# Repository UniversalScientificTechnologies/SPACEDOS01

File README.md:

# SPACEDOS01B - Cosmic-ray spectrometer and dosimeter for unmanned spacecraft missions

SPACEDOS01B is a semiconductor-based dosimeter launched at Sokrat-R (NORAD ID 44404) satellite, currently orbiting the Earth about 500km above the surface.
The device is intended for the measurement of cosmic radiation in mixed ionization fields on board satellites. In the case of manned missions look to [SPACEDOS02](https://github.com/UniversalScientificTechnologies/SPACEDOS02) or [SPACEDOS03](https://github.com/UniversalScientificTechnologies/SPACEDOS03).

The device can be purchased from Universal Scientific Technologies s.r.o. Contact us by email at sale@ust.cz for a commercial quotation.

### The main technical parameters are the following

* Silicon PIN diode detector with ~12.5 mm³ detection volume
* Measurement environment: vacuum < 3.2×10e−2 Pa
* Number of energy channels: 250
* Deposited energy range: from 200 keV to 12 MeV
* Energy measurement resolution: < 50 keV/channel
* Power supply: 3.3 V / 3 mA
* Integration time: 15 s
* Interface: RS232 TTL
* Dimensions(HxWxL): 15mm x 41mm x 94 mm
* Weight 33 g

[Technical documentation](https://docs.dos.ust.cz/spacedos/SPACEDOS01)

## References

  * [SPACEDOS dosimeter from the NPI became a part of the Cosmos Discovery exhibition](http://www.ujf.cas.cz/en/news/SPACEDOS-dosimeter-from-the-NPI-became-a-part-of-the-Cosmos-Discovery-exhibition/)
  * [SPACEDOS an open-source PIN diode dosimeter for applications in Space](https://indico.ujf.cas.cz/event/2/contributions/27/attachments/25/46/Po-1315-Kakona-774711333.pdf)

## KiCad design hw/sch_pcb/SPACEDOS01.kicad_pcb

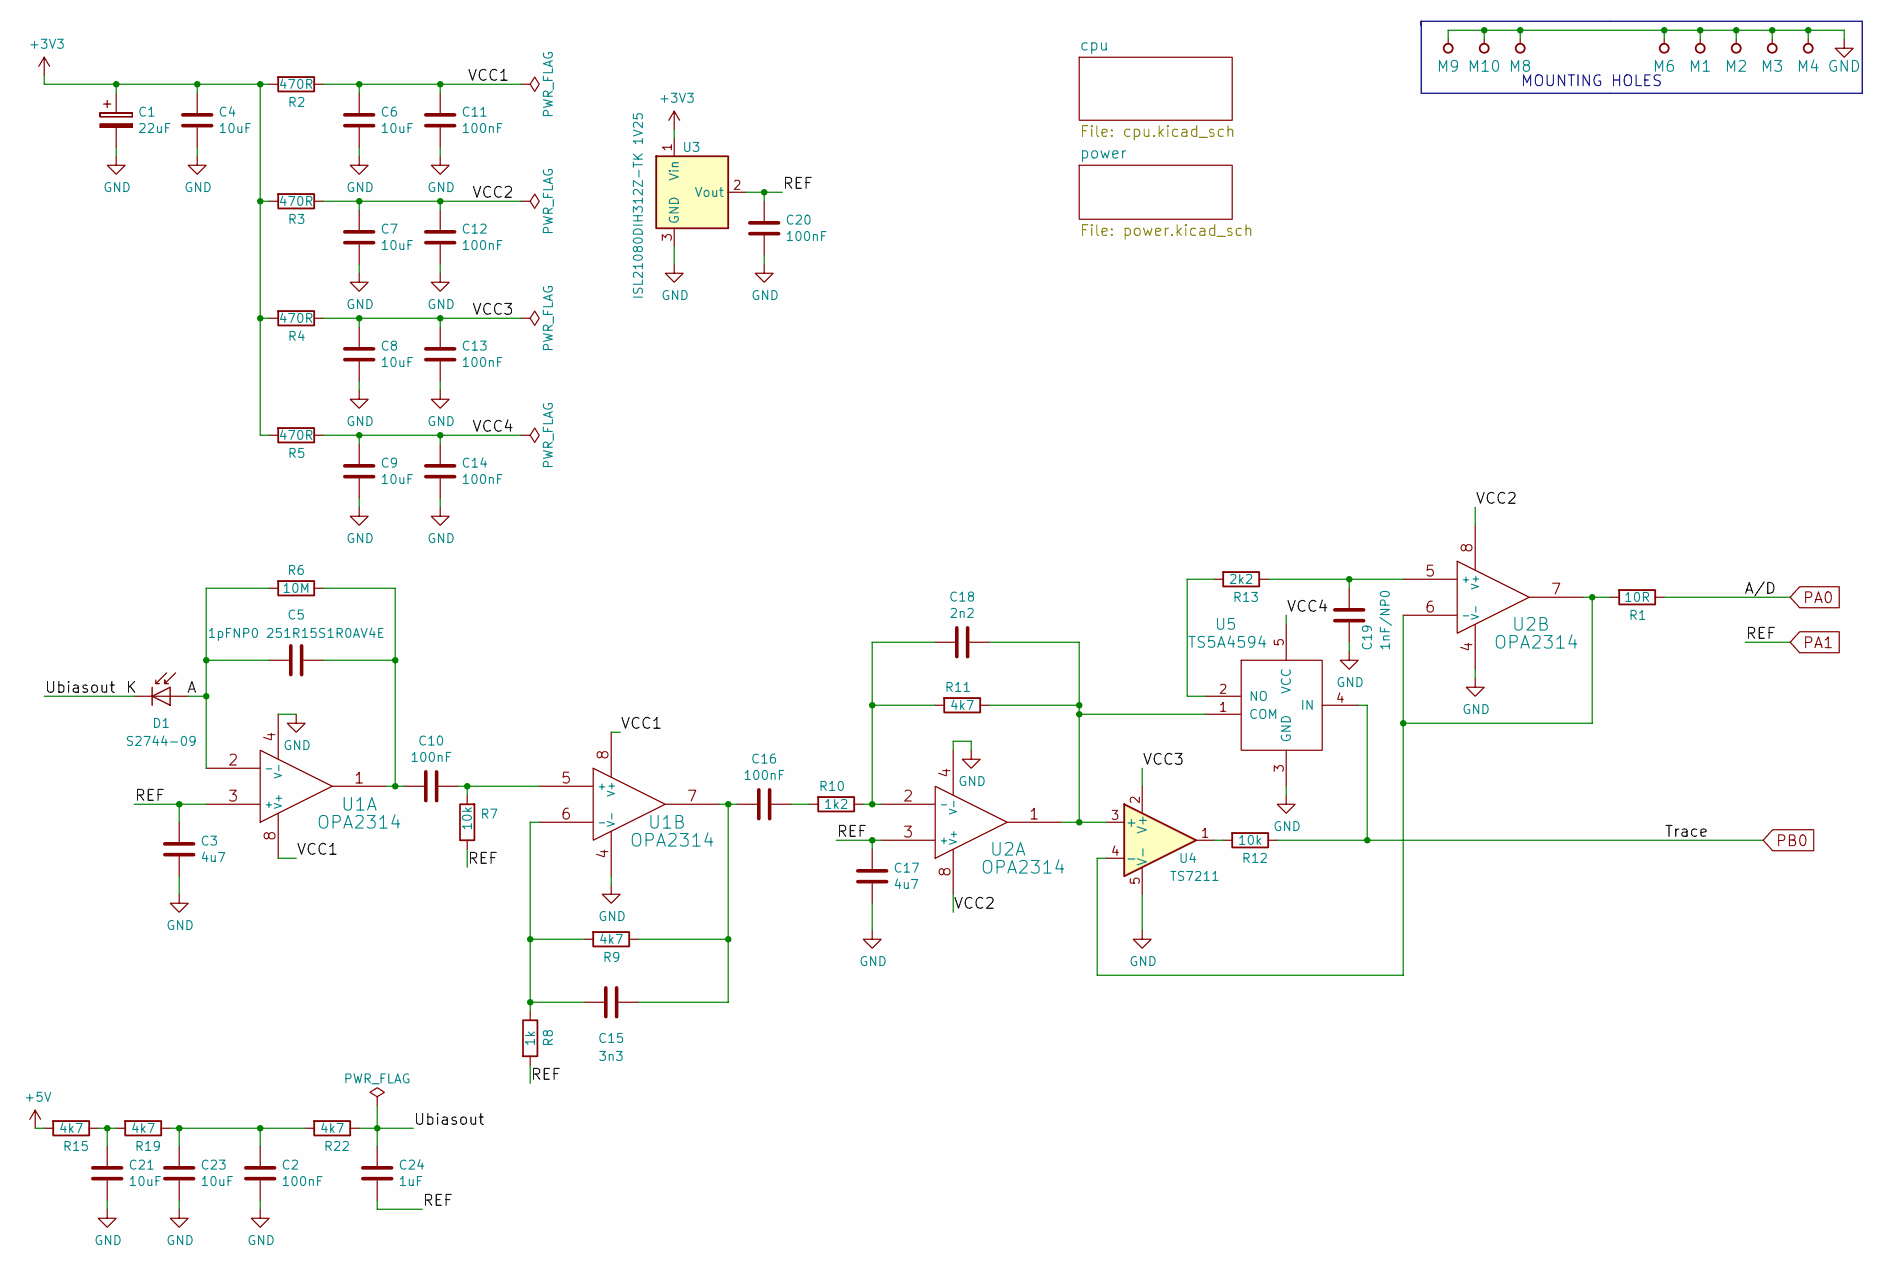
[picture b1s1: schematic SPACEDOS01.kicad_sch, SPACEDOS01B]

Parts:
C1: 22uF; TantalC_SizeC_Reflow
C2, C10, C11, C12, C13, C14, C16, C20: 100nF; SMD-0805
C3, C17: 4u7; SMD-0805
C4, C6, C7, C8, C9, C21, C23: 10uF; SMD-0805
C5: 1pFNP0 251R15S1R0AV4E; SMD-0805
C15: 3n3; SMD-0805
C18: 2n2; SMD-0805
C19: 1nF/NP0; SMD-0805
C24: 1uF; SMD-0805
D1: S2744-09; HAMAMATSU_S11773-02
M1, M2, M3, M4: HOLE; MountingHole_3mm
M6: BMI-S-210-F
M8, M9, M10: BMI-S-204-F; Laird_Technologies_BMI-S-204-F_32.00x32.00mm
R1: 10R; SMD-0805
R2, R3, R4, R5: 470R; SMD-0805
R6: 10M; SMD-0805
R7, R12: 10k; SMD-0805
R8: 1k; SMD-0805
R9, R11, R15, R19, R22: 4k7; SMD-0805
R10: 1k2; SMD-0805
R13: 2k2; SMD-0805
U1, U2: OPA2314; SOIC-8_3.9x4.9mm_Pitch1.27mm
U3: ISL21080DIH312Z-TK 1V25; SOT-23
U4: TS7211; SOT-23-5_HandSoldering
U5: TS5A4594; SOT-23-5_HandSoldering

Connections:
+3V3: C1.1, C4.1, R2.2, R3.2, R4.2, R5.2, U3.1 (Vin); also elsewhere on the board
+5V: R15.2; also elsewhere on the board
/A: C5.2, D1.2 (A), R6.2, U1.2 (-)
/K: C24.1, D1.1 (K), R22.1
/VCC1: C6.1, C11.1, R2.1, U1.8 (V+)
/VCC2: C7.1, C12.1, R3.1, U2.8 (V+)
/VCC3: C8.1, C13.1, R4.1, U4.2 (V+)
/VCC4: C9.1, C14.1, R5.1, U5.5 (VCC)
GND: C1.2, C2.2, C3.2, C4.2, C6.2, C7.2, C8.2, C9.2, C11.2, C12.2, C13.2, C14.2, C17.2, C19.2, C20.2, C21.2, C23.2, M1.1, M2.1, M3.1, M4.1, M6.1, M8.1, M9.1, M10.1, U1.4 (V-), U2.4 (V-), U3.3 (GND), U4.5 (V-), U5.3 (GND); also elsewhere on the board
unnamed: C2.1, C23.1, R19.1, R22.2
unnamed: C5.1, C10.2, R6.1, U1.1
unnamed: C15.1, C16.2, R9.1, U1.7
unnamed: C16.1, R10.2
unnamed: C21.1, R15.1, R19.2
unnamed: R12.2, U4.1
unnamed: C10.1, R7.2, U1.5 (+)
unnamed: C15.2, R8.1, R9.2, U1.6 (-)
unnamed: C18.2, R10.1, R11.2, U2.2 (-)
unnamed: C19.1, R13.1, U2.5 (+)
unnamed: R1.2, U2.6 (-), U2.7, U4.4 (-)
unnamed: C18.1, R11.1, U2.1, U4.3 (+), U5.1 (COM)
unnamed: R13.2, U5.2 (NO)
PA0: R1.1; also elsewhere on the board
PA1: C3.1, C17.1, C20.1, C24.2, R7.1, R8.2, U1.3 (+), U2.3 (+), U3.2 (Vout); also elsewhere on the board
PB0: R12.1, U5.4 (IN); also elsewhere on the board

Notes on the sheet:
MOUNTING HOLES

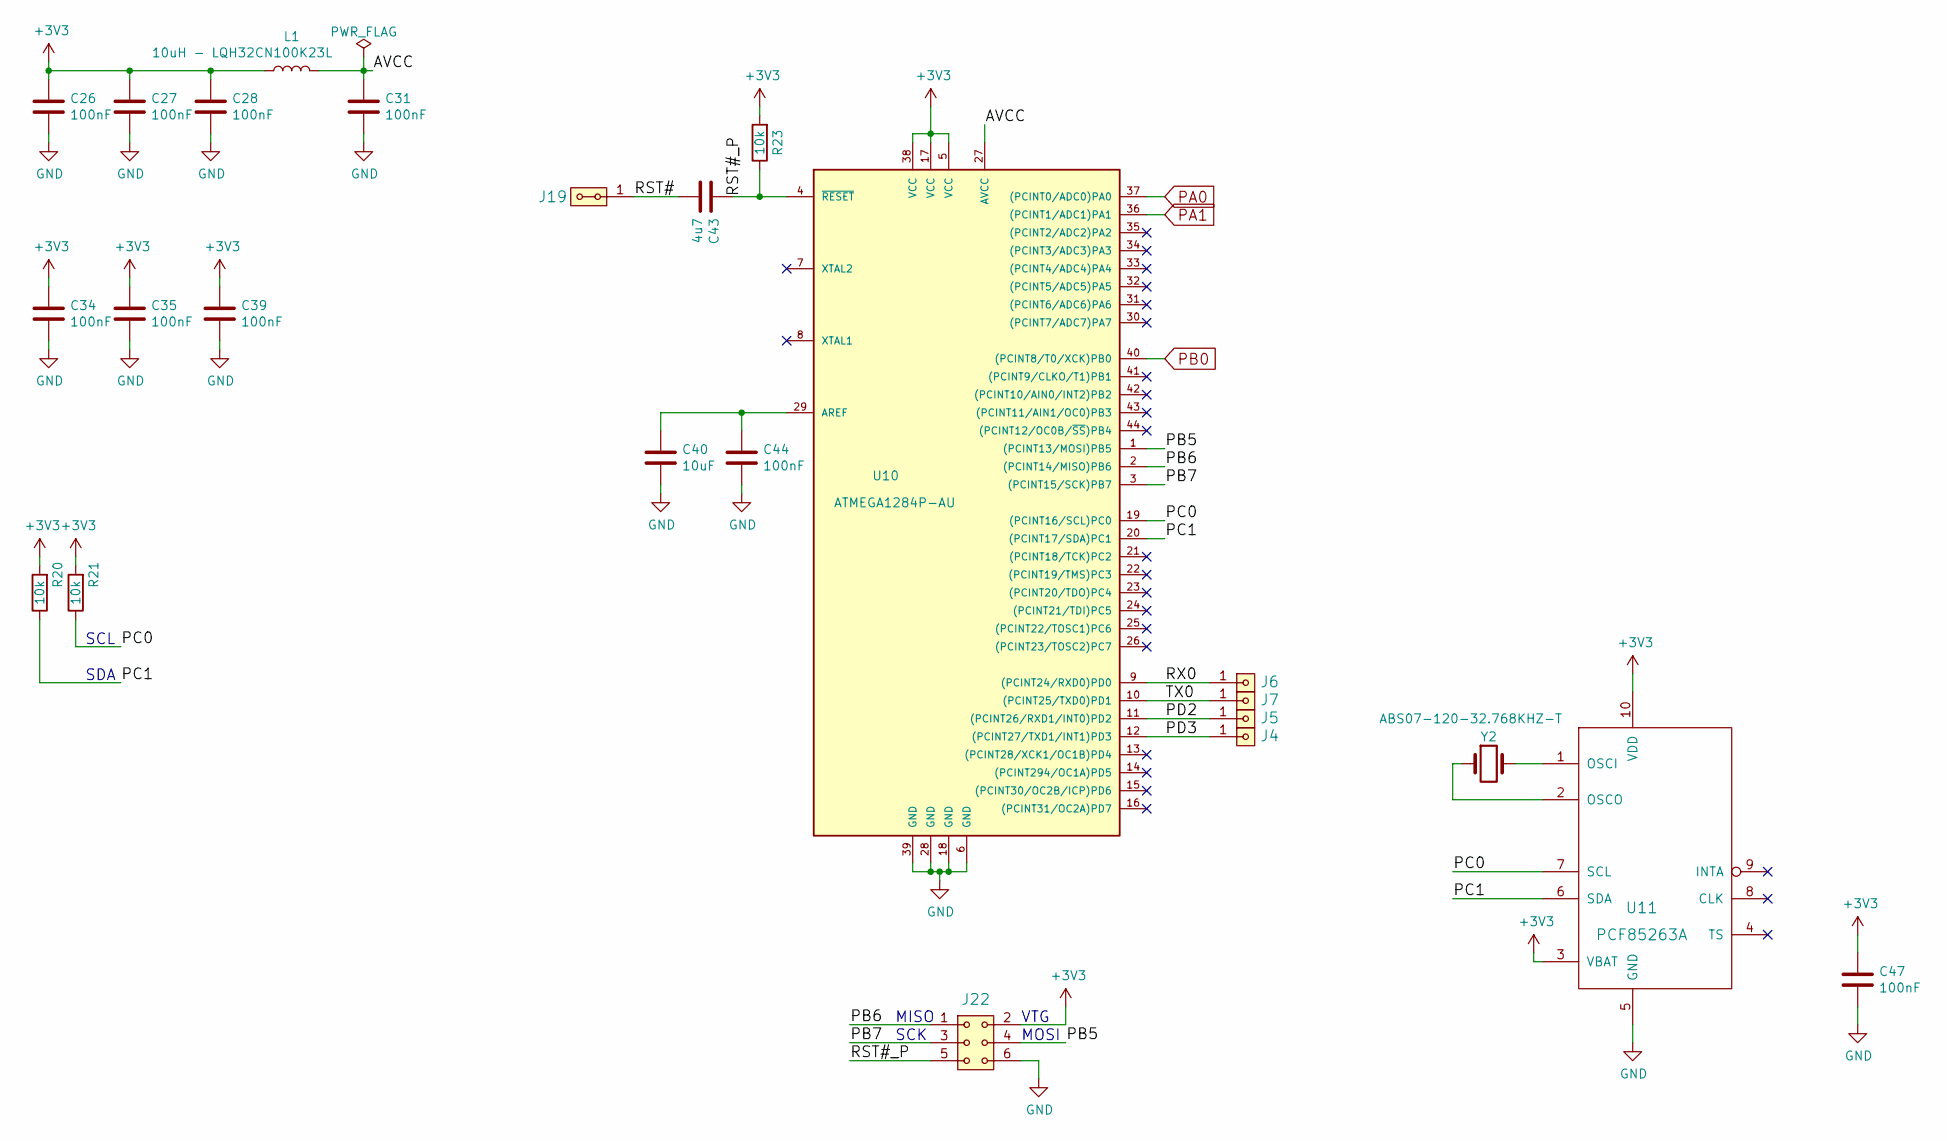
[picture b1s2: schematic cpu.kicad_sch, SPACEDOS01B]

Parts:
C26, C27, C28, C31, C34, C35, C39, C44, C47: 100nF; SMD-0805
C40: 10uF; SMD-0805
C43: 4u7; SMD-0805
J4, J5, J6, J7: HEADER_1x01; Straight_1x01
J19: HEADER_2x01_PARALLEL; Straight_2x01
J22: HEADER_2x03; SMD_2x03
L1: 10uH - LQH32CN100K23L; SMD-1210
R20, R21, R23: 10k; SMD-0805
U10: ATMEGA1284P-AU; TQFP-44_10x10mm_P0.8mm
U11: PCF85263A; TSSOP-10_3x3mm_Pitch0.5mm
Y2: ABS07-120-32.768KHZ-T; ABS07

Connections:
+3V3: C26.1, C27.1, C28.1, C34.1, C35.1, C39.1, C47.1, J22.2, L1.1, R20.2, R21.2, R23.2, U10.5 (VCC), U10.17 (VCC), U10.38 (VCC), U11.3 (VBAT), U11.10 (VDD); also elsewhere on the board
/cpu/AVCC: C31.1, L1.2, U10.27 (AVCC)
/cpu/PB5: J22.4, U10.1 ((PCINT13/MOSI)PB5)
/cpu/PB6: J22.1, U10.2 ((PCINT14/MISO)PB6)
/cpu/PB7: J22.3, U10.3 ((PCINT15/SCK)PB7)
/cpu/PC0: R21.1, U10.19 ((PCINT16/SCL)PC0), U11.7 (SCL)
/cpu/PC1: R20.1, U10.20 ((PCINT17/SDA)PC1), U11.6 (SDA)
/cpu/PD2: J5.1, U10.11 ((PCINT26/RXD1/INT0)PD2)
/cpu/PD3: J4.1, U10.12 ((PCINT27/TXD1/INT1)PD3)
/cpu/RST#: C43.2, J19.1, J19.2
/cpu/RST#_P: C43.1, J22.5, R23.1, U10.4 (~RESET)
/cpu/RX0: J6.1, U10.9 ((PCINT24/RXD0)PD0)
/cpu/TX0: J7.1, U10.10 ((PCINT25/TXD0)PD1)
GND: C26.2, C27.2, C28.2, C31.2, C34.2, C35.2, C39.2, C40.2, C44.2, C47.2, J22.6, U10.6 (GND), U10.18 (GND), U10.28 (GND), U10.39 (GND), U11.5 (GND); also elsewhere on the board
unnamed: C40.1, C44.1, U10.29 (AREF)
unnamed: U11.1 (OSCI), Y2.2
unnamed: U11.2 (OSCO), Y2.1
PA0: U10.37 ((PCINT0/ADC0)PA0); also elsewhere on the board
PA1: U10.36 ((PCINT1/ADC1)PA1); also elsewhere on the board
PB0: U10.40 ((PCINT8/T0/XCK)PB0); also elsewhere on the board

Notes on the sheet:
SCL
MISO
MOSI
SCK
SDA
VTG

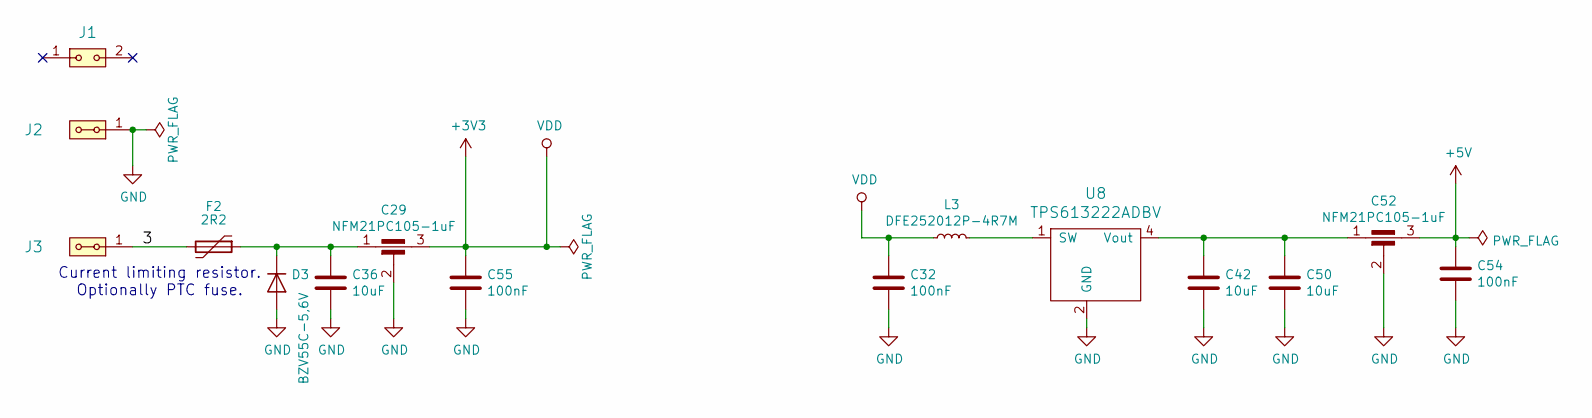
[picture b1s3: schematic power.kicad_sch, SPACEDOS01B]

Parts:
C29, C52: NFM21PC105-1uF; FIR_0805
C32, C54, C55: 100nF; SMD-0805
C36, C42, C50: 10uF; SMD-0805
D3: BZV55C-5,6V; D_MiniMELF
F2: 2R2; SMD-0805
J1: HEADER_2x01; Straight_1x02
J2, J3: HEADER_2x01_PARALLEL; Straight_1x02
L3: DFE252012P-4R7M; R_0805_2012Metric_Pad1.15x1.40mm_HandSolder
U8: TPS613222ADBV; SOT-23-5

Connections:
+3V3: C29.3, C32.1, C55.1, L3.1; also elsewhere on the board
+5V: C52.3, C54.1; also elsewhere on the board
/power/3: F2.2, J3.1, J3.2
GND: C29.2, C32.2, C36.2, C42.2, C50.2, C52.2, C54.2, C55.2, D3.2 (A), J2.1, J2.2, U8.2 (GND); also elsewhere on the board
unnamed: C29.1, C36.1, D3.1 (K), F2.1
unnamed: L3.2, U8.1 (SW)
unnamed: C42.1, C50.1, C52.1, U8.4 (Vout)

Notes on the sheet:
Current limiting resistor. Optionally PTC fuse.

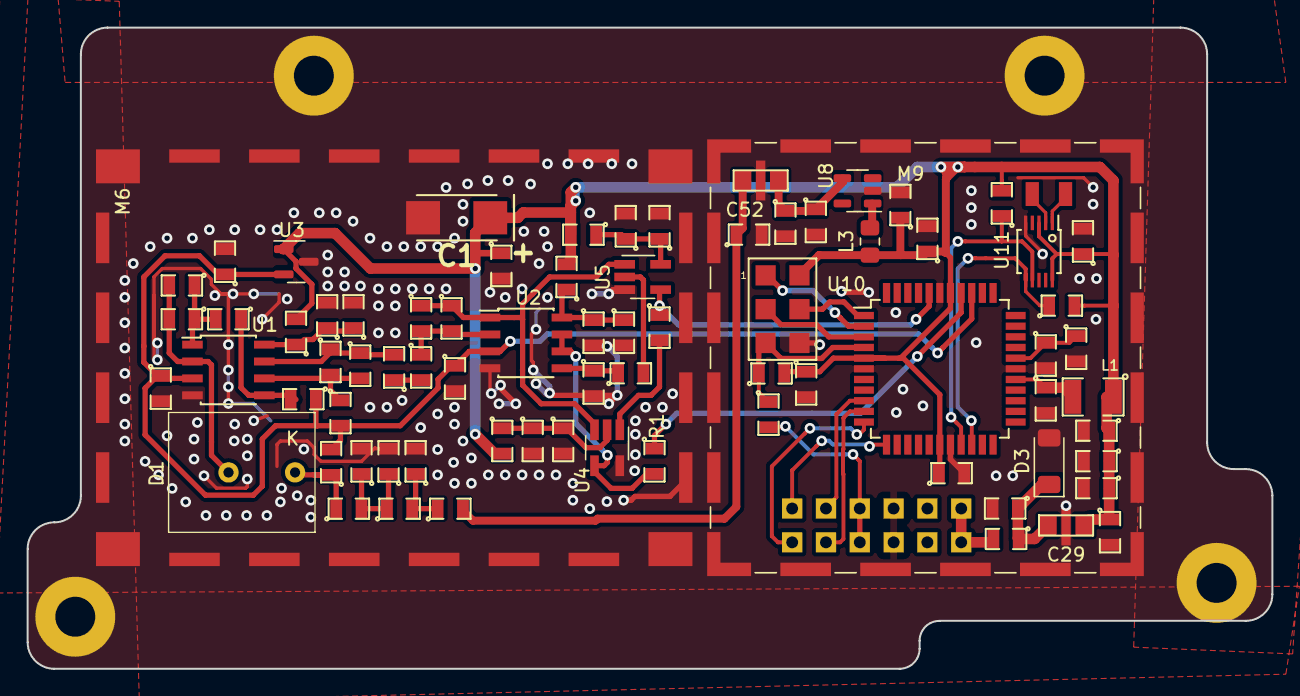
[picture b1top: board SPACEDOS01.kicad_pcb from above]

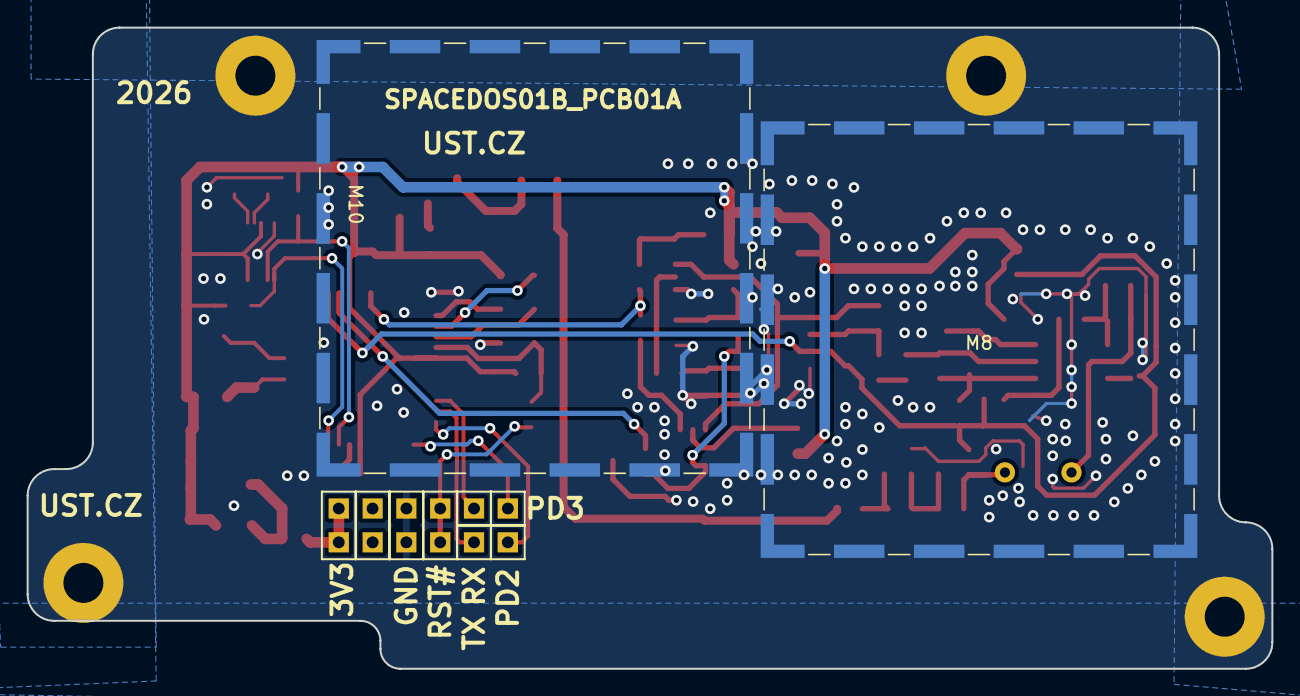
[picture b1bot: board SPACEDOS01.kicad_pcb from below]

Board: 2 copper layers, 93.5 x 48.2 mm, 92 parts (10 on the bottom side), 44 nets.

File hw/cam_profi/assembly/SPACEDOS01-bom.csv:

Component,Description,Part,References,Value,Footprint,Quantity Per PCB,Datasheet,ust_id
1,,C,C18,2n2,SMD-0805,1,~,5c70984712875079b91f8b46
2,,C,C15,3n3,SMD-0805,1,~,5c70984712875079b91f8b47
3,,C,C2C10C11C12C13C14C16C20,100nF,SMD-0805,8,,5c70984712875079b91f8b4c
4,,C-device-DATALOGGER01A-rescue-CCP2019V01A-rescue-SPACEDOS01A_PCB01A-rescue,C26C27C28C31C32C34C35C39C44C47C54C55,100nF,SMD-0805,12,,5c70984712875079b91f8b4c
5,,C,C24,1uF,SMD-0805,1,~,5c70984712875079b91f8b50
6,,C,C3C17,4u7,SMD-0805,2,~,5e3ff8fc1287502a33bad7a3
7,,C-device-DATALOGGER01A-rescue-CCP2019V01A-rescue-SPACEDOS01A_PCB01A-rescue,C43,4u7,SMD-0805,1,,5e3ff8fc1287502a33bad7a3
8,,C,C4C6C7C8C9C21C23,10uF,SMD-0805,7,~,5c70984712875079b91f8b53
9,,C-device-DATALOGGER01A-rescue-CCP2019V01A-rescue-SPACEDOS01A_PCB01A-rescue,C36C40C42C50,10uF,SMD-0805,4,,5c70984712875079b91f8b53
10,,CP,C1,22uF,TantalC_SizeC_Reflow,1,~,650b58f1462c6d9e7205463b
11,,C,C19,1nF/NP0,SMD-0805,1,~,5c70984812875079b91f8ba6
12,,C,C5,1pFNP0 251R15S1R0AV4E,SMD-0805,1,~,5c70984712875079b91f8b9f
13,,EMI_Filter_C-device-DATALOGGER01A-rescue-CCP2019V01A-rescue-SPACEDOS01A_PCB01A-rescue,C29C52,NFM21PC105-1uF,FIR_0805,2,http://www.murata.com/~/media/webrenewal/support/library/cat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,5c70984412875079b91f880f
14,,D-device-DATALOGGER01A-rescue-CCP2019V01A-rescue-SPACEDOS01A_PCB01A-rescue,D3,"BZV55C-5,6V",D_MiniMELF,1,,5c70984512875079b91f88b2
15,,D_Photo,D1,S2744-09,HAMAMATSU_S11773-02,1,~,628d118cdc56076e9a2235e4
16,,Polyfuse-device-DATALOGGER01A-rescue-CCP2019V01A-rescue-SPACEDOS01A_PCB01A-rescue-SPACEDOS01B_PCB01A-rescue,F2,2R2,SMD-0805,1,,5cac42d21287500e61c241e5
17,,L-device-DATALOGGER01A-rescue-CCP2019V01A-rescue-SPACEDOS01A_PCB01A-rescue,L1,10uH - LQH32CN100K23L,SMD-1210,1,,5c70984412875079b91f87ff
18,,L_Small,L3,DFE252012P-4R7M,R_0805_2012Metric_Pad1.15x1.40mm_HandSolder,1,~,5cc3309d128750448e54e8d8
19,,HOLE,M8M9M10,BMI-S-204-F,Laird_Technologies_BMI-S-204-F_32.00x32.00mm,3,,5c72751c1287500b4e11301a
20,,HOLE,M6,BMI-S-210-F,BMI-S-210-F,1,,5c70984312875079b91f873d
21,,R,R1,10R,SMD-0805,1,~,5c70984512875079b91f896d
22,,R,R2R3R4R5,470R,SMD-0805,4,~,5c70984512875079b91f8986
23,,R,R8,1k,SMD-0805,1,~,5c70984512875079b91f898c
24,,R,R10,1k2,SMD-0805,1,~,5c70984512875079b91f898d
25,,R,R13,2k2,SMD-0805,1,~,5c70984612875079b91f8990
26,,R,R9R11R15R19R22,4k7,SMD-0805,5,~,5c70984612875079b91f8995
27,,R,R7R12,10k,SMD-0805,2,~,5c70984612875079b91f899f
28,,R-device-DATALOGGER01A-rescue-CCP2019V01A-rescue-SPACEDOS01A_PCB01A-rescue,R20R21R23,10k,SMD-0805,3,,5c70984612875079b91f899f
29,,R,R6,10M,SMD-0805,1,~,5c70984712875079b91f8aae
30,,ATMEGA1284P-AU-atmel-DATALOGGER01A-rescue-CCP2019V01A-rescue-SPACEDOS01A_PCB01A-rescue,U10,ATMEGA1284P-AU,TQFP-44_10x10mm_P0.8mm,1,http://www.atmel.com/Images/Atmel-8272-8-bit-AVR-microcontro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,5c70984712875079b91f8b5b
31,,ISL21070CIH320Z-TK,U3,ISL21080DIH312Z-TK  1V25,SOT-23,1,https://eu.mouser.com/datasheet/2/698/REN_isl21080_DST_20040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,5c70984712875079b91f8b7a
32,,AD8692,U1U2,OPA2314,SOIC-8_3.9x4.9mm_Pitch1.27mm,2,,5c70984412875079b91f879b
33,,PCF85263A,U11,PCF85263A,TSSOP-10_3x3mm_Pitch0.5mm,1,,5c70984612875079b91f8a0c
34,,TPS61322xA,U8,TPS613222ADBV,SOT-23-5,1,https://www.ti.com/lit/ds/symlink/tps61322.pdf,5c7190ae1287500b4e112e04
35,,TS5A4594,U5,TS5A4594,SOT-23-5_HandSoldering,1,,5c70984612875079b91f8a0d
36,,OP179GRT,U4,TS7211,SOT-23-5_HandSoldering,1,http://www.analog.com/media/en/technical-documentation/data-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,5c70984712875079b91f8b5b
37,,Crystal-device-DATALOGGER01A-rescue-CCP2019V01A-rescue-SPACEDOS01A_PCB01A-rescue,Y2,ABS07-120-32.768KHZ-T,ABS07,1,,5c70984712875079b91f8b1b

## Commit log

2019-01-30 New PCB
2019-01-30 edit
2019-02-11 first version for integration by ESC
2019-02-11 picture
2019-02-11 physical dimensions
2019-02-11 new picture
2019-02-11 connector header
2019-02-13 STEP and WRML models ware added
2019-02-27 test version with beacon data and almanac data
2019-03-01 Cvak, Hmmm to
2019-03-01 all hexadecimal output
2019-03-01 bath for githas renewing
2019-03-01 githash test
2019-03-06 edit PCB
2019-03-07 version hash scripts
2019-03-07 STEP format was generated
2019-03-11 pictures of version 01B
2019-03-14 with one day periodicity
2019-03-14 FW for calibration and gitattributes for branch master
2019-03-14 new GPIO ports definition for SPACEDOS01B
2019-03-14 bat name of .gitattributes
2019-07-03 Update of device photos.
2019-07-03 Removing old photo.
2020-11-24 Edit PCB SPACEDOS01A_PCB01B
2020-11-25 Editace PCB a generování vyrobních dat.
2020-12-19 Přidání souboru pro napsání návodu na nastavení
2020-12-19 Přidány obrázky pro návod.
2020-12-19 Příprva obrázku pro připojení programátoru
2021-11-08 Update stylesheet.
2021-12-10 Move wiki pages documentation to github pages.
2021-12-10 Set theme jekyll-theme-cayman
2021-12-10 Move the github pages files to github compatible directory name.
2021-12-10 Configure github pages.
2021-12-10 use github friendly documentation directory naming convention.
2021-12-10 Update kicad project and schematics PDF export.
2021-12-13 Rename Home.md to Index.md
2021-12-13 Rename Index.md to index.md
2021-12-13 copy immages
2021-12-13 Create CNAME
2022-04-12 submodule, actions
2022-06-29 Update README.md
    Translation update
2023-01-25 deduplicate documentation.
2023-01-25 Removing unused file.
2023-01-25 removing unused file
2023-01-25 Remove unused file.
2023-01-25 Delete index.md
    Remove duplicated documentation.
2023-01-25 Delete _config.yml
    Remove GitHub pages configuration.
2023-01-25 Update README.md
    Adding the link to the more detailed technical page.
2023-01-25 Update SPACEDOS01B.md
    Remove GitHub wiki artifacts.
2023-01-25 Update SPACEDOS01A.md
    Remove GitHub wiki artifacts.
2023-01-26 Update designs to KiCAD 6. Update schematics datasheet links Minor schematics improvements (titleblocks, schematics layout)
2023-01-26 Correcly setup automation workflows and cleanup KiCAD project.
2023-01-26 Update kicad_outputs.yml
    Fix the wrong path.
2023-01-26 Update actions products
2023-09-01 Update README.md
    Correct the measurement volume.
2024-02-09 Update SPACEDOS01B.md
    grammar check
2024-02-09 Update project files.
2024-02-09 Cleanup documentation.
2024-02-09 Center PCB in page. Improve dimensions.
2024-02-09 Update workflows.
2024-02-09 Project renamed to allow use of standard workflow.
2024-02-09 Updated PCB dimensions.
2024-02-09 Improve documentation image.
2024-02-10 Update workflow files
2024-02-17 Update image metadata.
2025-12-15 update ustid
2025-12-15 update actions"
2025-12-15 update firmware project to pio
2026-01-30 Update titleblock to fix schematics PDF generation. Improve schematics layout.
2026-01-31 Improve schematics desription.
2026-03-08 add development and testing scriptis
2026-03-12 Update project. Update components IDs
2026-03-18 version as delivered
